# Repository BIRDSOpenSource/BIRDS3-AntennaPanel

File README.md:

# BIRDS3-AntennaPanel
 Documentation for the Antenna Panel used in the BIRDS3 Satellite

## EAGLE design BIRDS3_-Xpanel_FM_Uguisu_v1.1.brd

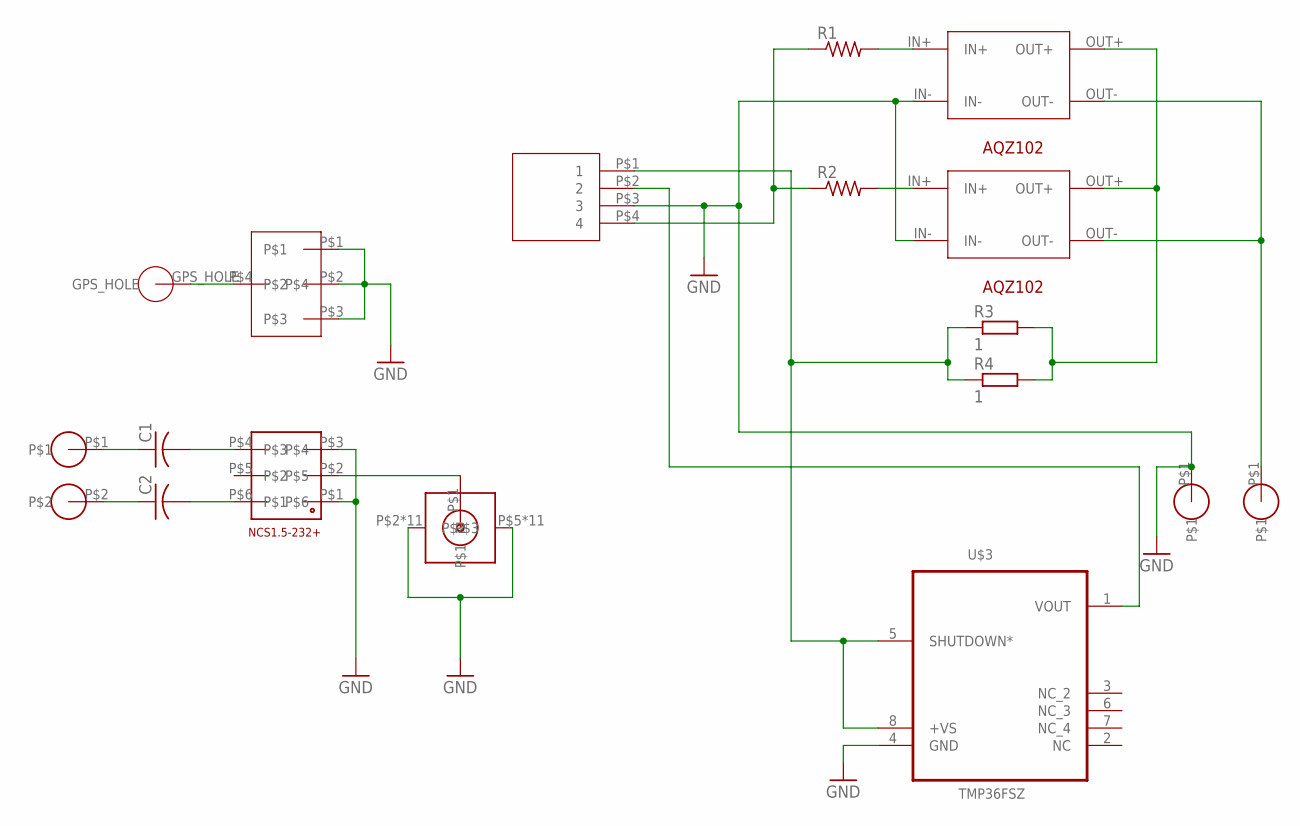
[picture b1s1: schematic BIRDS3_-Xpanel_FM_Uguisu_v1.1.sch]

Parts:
142_0711_1: SMA_142_0711_301
C1, C2: C-USC1608; C1608
GPS1: GPS_HOLE
K1, K2: DIODE_X; DIOD_X
MMCX1: MMCX_GPS
NCS1: NCS1.5-232+
PRE1: FOR_DIPOLE
R1, R2: R-US_R0402; R0402
R3, R4: 1; R1218
U$1, U$4: NICR_HOLE
U$2: 4PIN_HEADER
U$3: TMP36FSZ; SOIC_N

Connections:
BC_TEMP_OUT: U$2.P$2 (2), U$3.1 (VOUT)
GND: 142_0711_1.P$2, 142_0711_1.P$3, 142_0711_1.P$4, 142_0711_1.P$5, 142_0711_1.P$6, 142_0711_1.P$7, 142_0711_1.P$8, 142_0711_1.P$9, 142_0711_1.P$10, 142_0711_1.P$11, 142_0711_1.P$12, 142_0711_1.P$13, 142_0711_1.P$14, 142_0711_1.P$15, 142_0711_1.P$16, 142_0711_1.P$17, 142_0711_1.P$18, 142_0711_1.P$19, 142_0711_1.P$20, 142_0711_1.P$21, 142_0711_1.P$22, 142_0711_1.P$23, K1.IN-, K2.IN-, MMCX1.P$1, MMCX1.P$2, MMCX1.P$3, NCS1.P$1, NCS1.P$3, U$2.P$3 (3), U$3.4 (GND), U$4.P$1
HOT: K1.OUT-, K2.OUT-, U$1.P$1
MAIN_PIC_DIO: R1.1, R2.1, U$2.P$4 (4)
unnamed: K2.IN+, R1.2
unnamed: K1.OUT+, K2.OUT+, R3.2, R4.2
unnamed: K1.IN+, R2.2
unnamed: 142_0711_1.P$1, NCS1.P$2
unnamed: C1.1, PRE1.P$1
unnamed: C1.2, NCS1.P$4
unnamed: C2.2, NCS1.P$6
unnamed: C2.1, PRE1.P$2
unnamed: GPS1.GPS_HOLE, MMCX1.P$4
SUP_UNREG_2: R3.1, R4.1, U$2.P$1 (1), U$3.5 (SHUTDOWN*), U$3.8 (+VS)

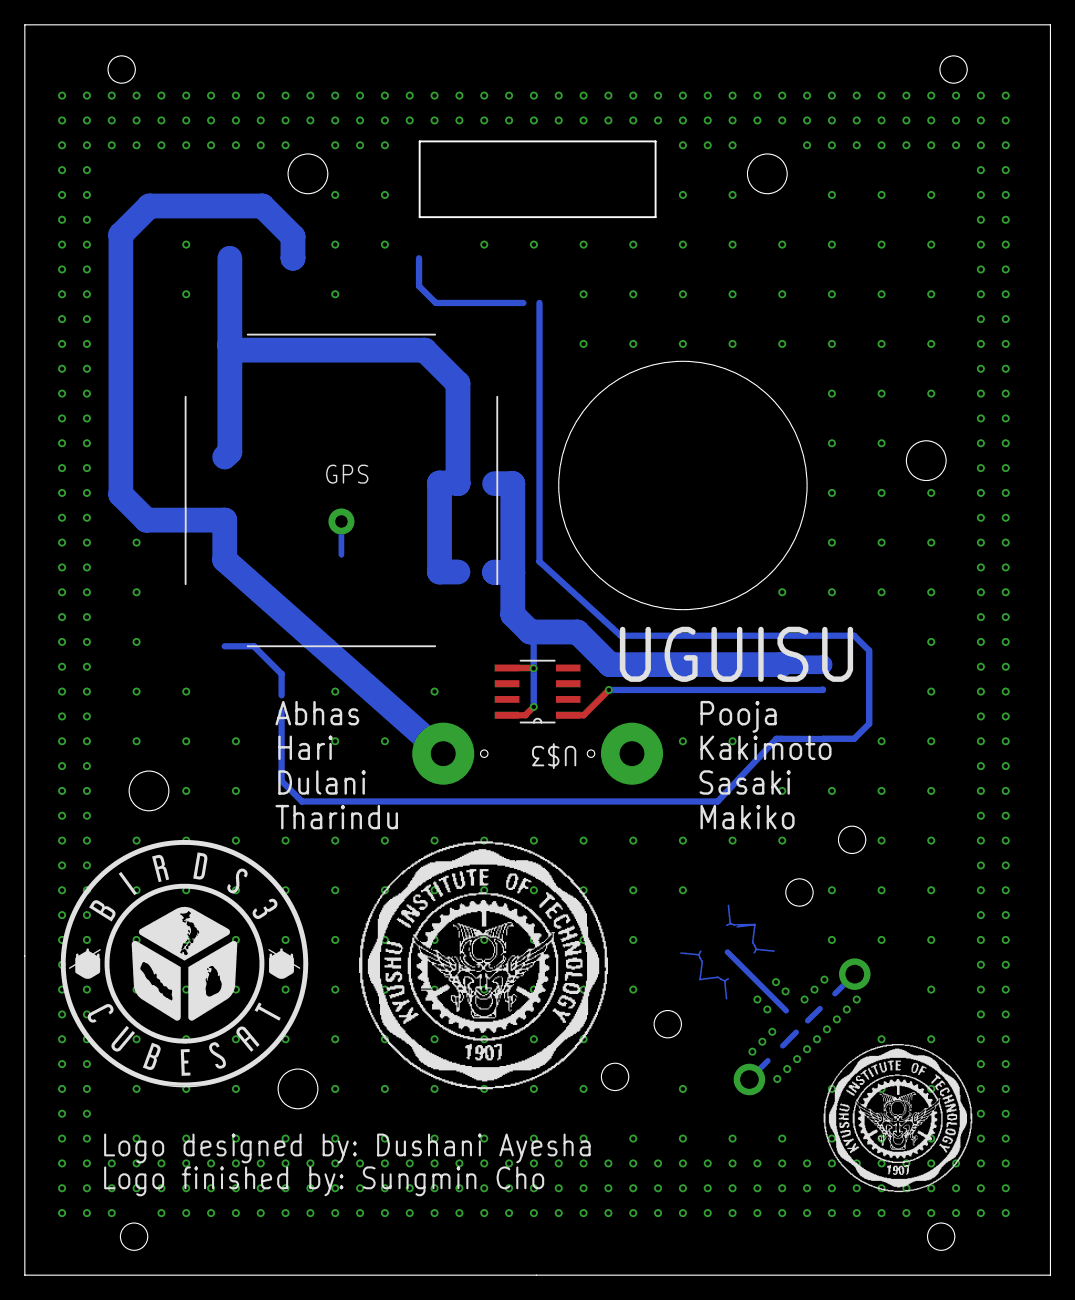
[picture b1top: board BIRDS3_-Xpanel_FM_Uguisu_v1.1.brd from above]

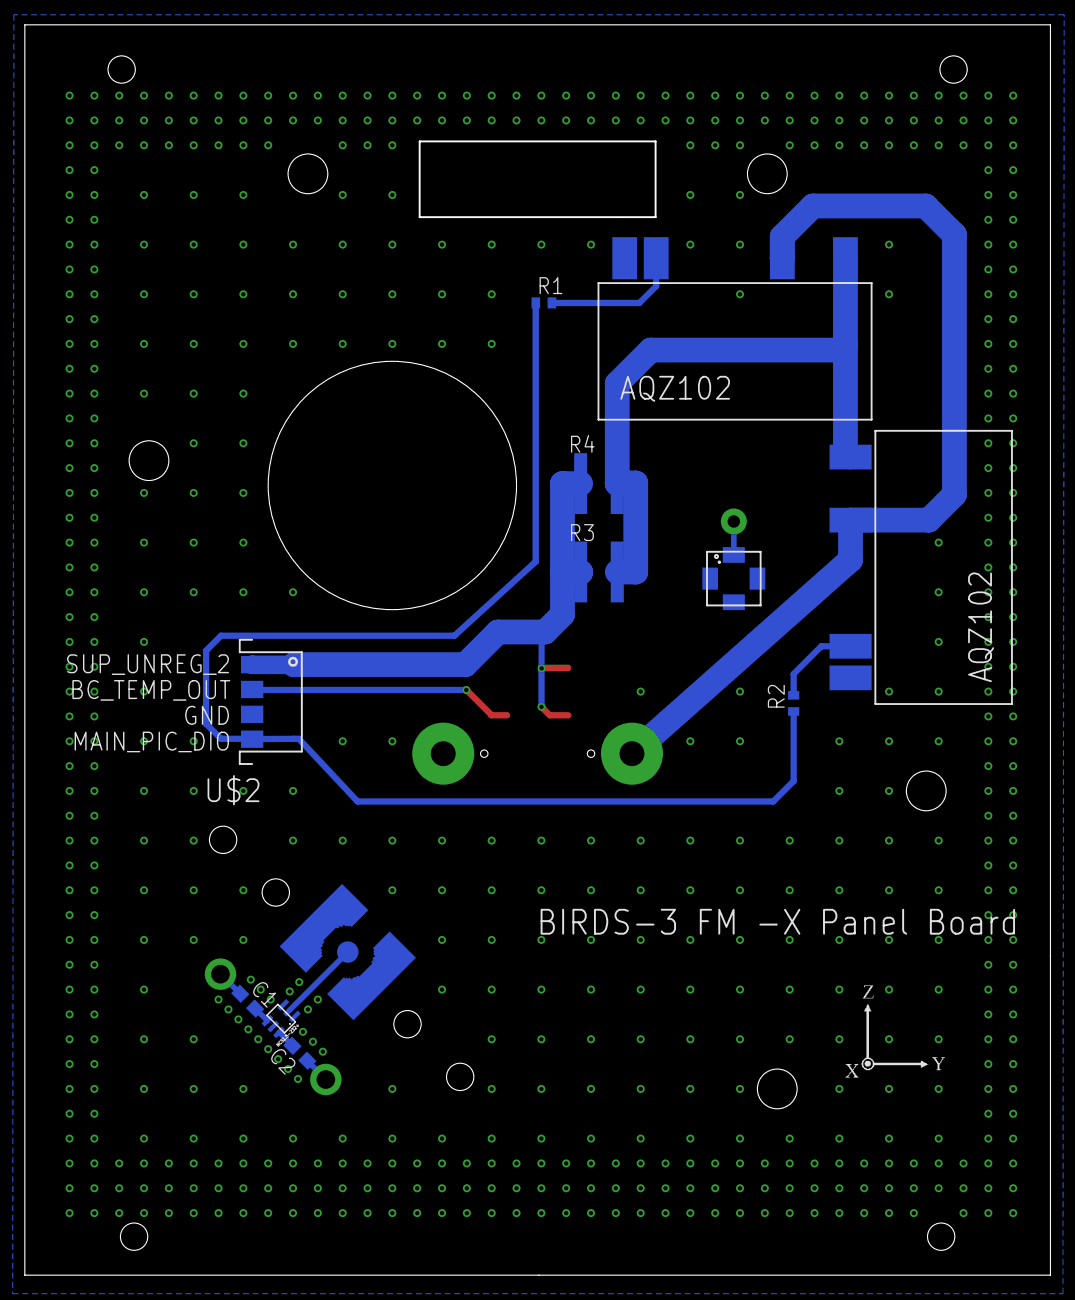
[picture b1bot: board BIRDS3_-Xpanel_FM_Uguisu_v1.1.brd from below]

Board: 4 copper layers, 82.4 x 100.5 mm, 17 parts (13 on the bottom side), 14 nets.

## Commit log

2021-10-05 Renamed partlist
2021-10-20 Update LICENSE
